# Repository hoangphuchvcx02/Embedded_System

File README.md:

#Embedded_System #LUONGHOANGPHUC #2010525
<!-- https://github.com/DenverCoder1/readme-typing-svg/blob/main/README.md?plain=1! -->
<!-- markdownlint-disable MD033 MD041 -->
<p align="center">
  <h3 align="center">⌨️ Readme First</h3>
</p>

## ⚡ Embedded System
In this course, I will upload exercise files, project, and simulations of embedded systems

```md
https://github.com/hoangphuchvcx02/Embedded_System/
```

## 🔧 Details

|  Folder  |                                   Details                                   |  Type   |            
| :---------------: | :----------------------------------------------------------------: | :-----: | 
|   `homework 1`    |   This exercise for creating schematic and layout, exporting manufacturing files using Kicad | homework  |

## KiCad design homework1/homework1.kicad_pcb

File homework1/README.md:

#homework1
## ⚡ Homework1
This exercise for creating schematic and layout, exporting manufacturing files using Kicad.
1. Follow the instruction in this video to create the schematic and layout for a LED Shield for Arduino

2. Create a git account, make a repository with name: Student_name-Student-ID-ESD-E1

3. Upload all the project files

4. From 3D image of the board, export to .png format for TOP view, BOTTOM view, side view and corner view. Upload them to the repository

5. Create a .txt file contain the git repository and submit to lms.

[Link to Schematic PDF](https://github.com/hoangphuchvcx02/LuongHoangPhuc_2010525_ESD-E1/blob/main/homework1/schematic.pdf)

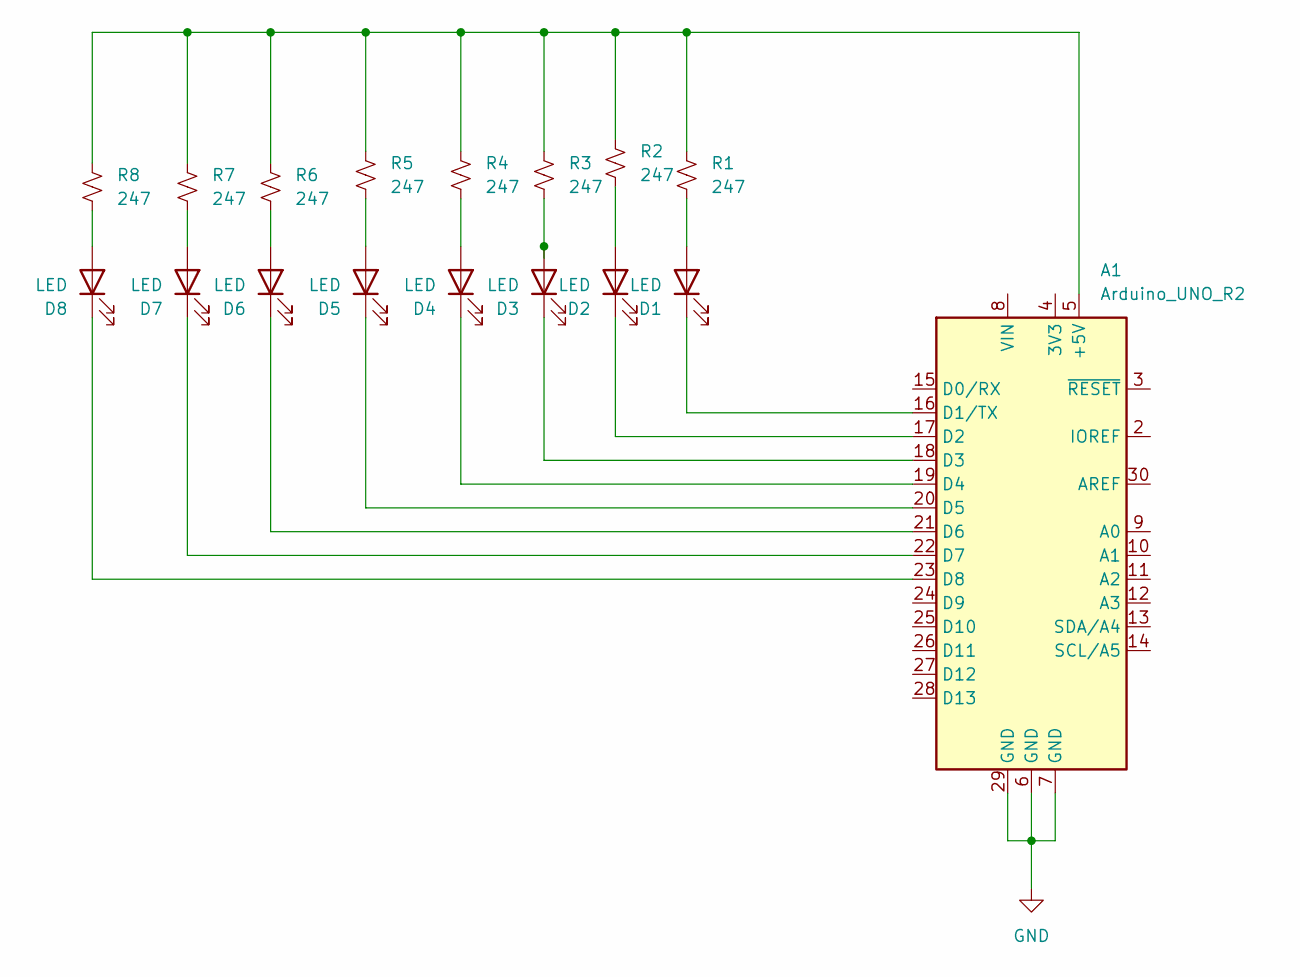
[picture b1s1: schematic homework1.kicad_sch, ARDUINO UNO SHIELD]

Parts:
A1: Arduino_UNO_R2
D1, D2, D3, D4, D5, D6, D7, D8: LED; LED_0805_2012Metric
R1, R2, R3, R4, R5, R6, R7, R8: 247; R_0603_1608Metric

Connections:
GND: A1.6 (GND), A1.7 (GND), A1.29 (GND)
unnamed: A1.5 (+5V), R1.1, R2.1, R3.1, R4.1, R5.1, R6.1, R7.1, R8.1
unnamed: A1.16 (D1/TX), D1.1 (K)
unnamed: A1.17 (D2), D2.1 (K)
unnamed: A1.18 (D3), D3.1 (K)
unnamed: A1.19 (D4), D4.1 (K)
unnamed: A1.20 (D5), D5.1 (K)
unnamed: A1.21 (D6), D6.1 (K)
unnamed: A1.22 (D7), D7.1 (K)
unnamed: A1.23 (D8), D8.1 (K)
unnamed: D1.2 (A), R1.2
unnamed: D2.2 (A), R2.2
unnamed: D3.2 (A), R3.2
unnamed: D4.2 (A), R4.2
unnamed: D5.2 (A), R5.2
unnamed: D6.2 (A), R6.2
unnamed: D7.2 (A), R7.2
unnamed: D8.2 (A), R8.2

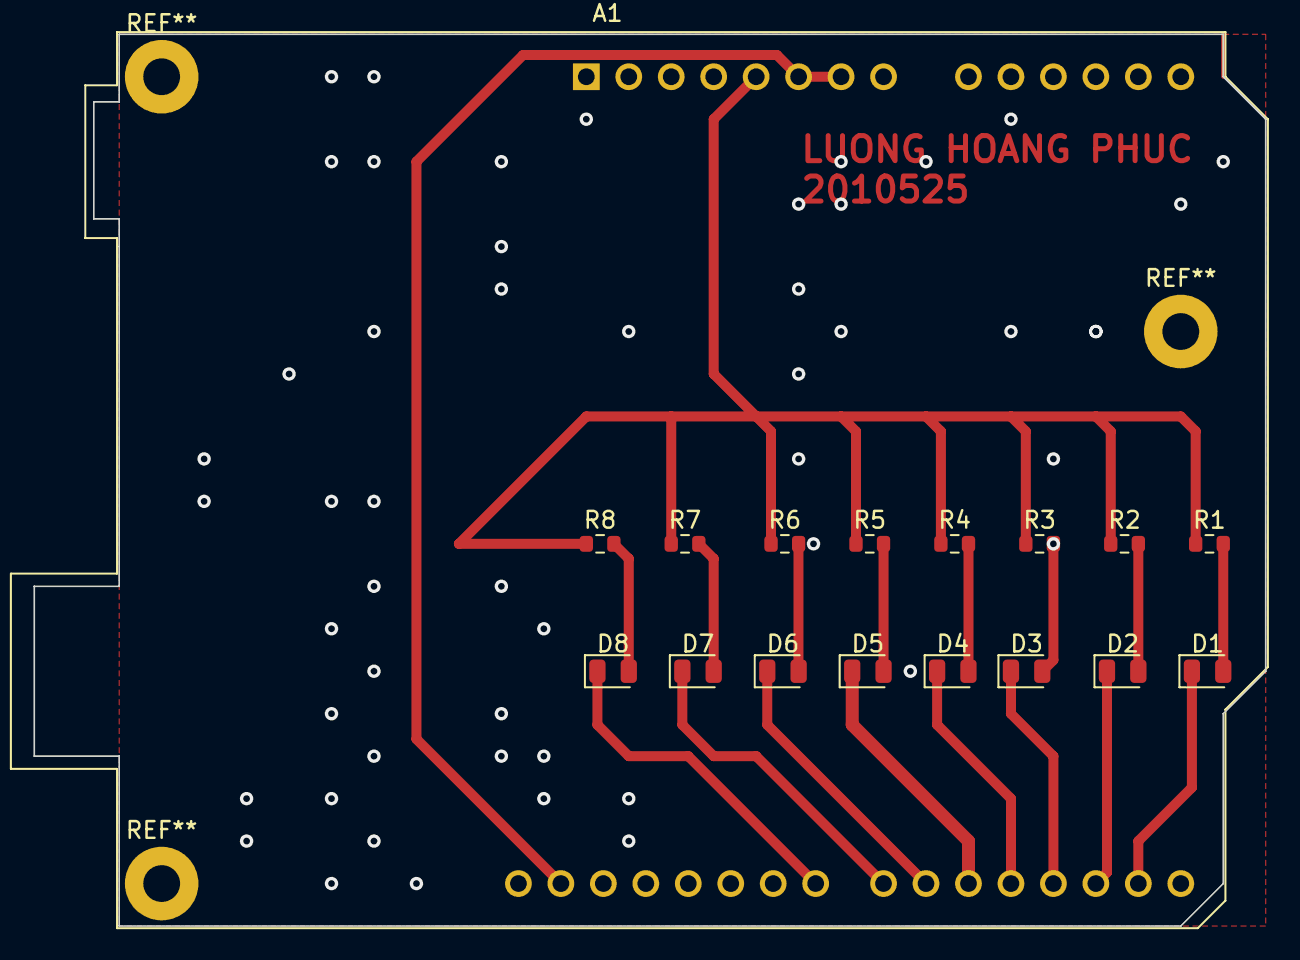
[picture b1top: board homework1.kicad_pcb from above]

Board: 2 copper layers, 73.7 x 53.3 mm, 17 parts (0 on the bottom side), 18 nets.

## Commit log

2024-01-21 lan 1
